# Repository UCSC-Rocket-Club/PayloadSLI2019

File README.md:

# Payload SLI 2019

## Summary
This is the code for deployment of the Payload for NASA's 2019 SLI Payload challenge. During flight, at approximately 400 feet, we will remotely trigger separation of the payload section via radio; and later trigger release of the drone. 

We are using the [Adafruit Feather LoRa 32u4 (RFM9x) with the RadioHead (RFM9x) library](https://learn.adafruit.com/adafruit-feather-32u4-radio-with-lora-radio-module/using-the-rfm-9x-radio). 

We are using the [Adafruit Micro-SD Breakout Board](https://cdn-learn.adafruit.com/downloads/pdf/adafruit-micro-sd-breakout-board-card-tutorial.pdf).

## Instructions to run
* Open the code in the Arduino IDE
* Follow [these steps](https://learn.adafruit.com/adafruit-feather-32u4-radio-with-lora-radio-module/setup) for installing the drivers for the Feather
* In `Arduino > Preferences`, under "Show verbose mode during" check both compilation and upload (this solves some issues with the board)
* Install the [RadioHead library](https://learn.adafruit.com/adafruit-feather-32u4-radio-with-lora-radio-module/using-the-rfm-9x-radio) (Note: Find the folder to put this in by going to Arduino -> Preferences -> Sketchbook location. Open this folder and there should be a folder called libraries in there. Put the unzipped library inside there.)

## Rules for this repo and all Payload code
* DO NOT SEND CODE OVER SLACK/IMESSAGE/FB
* Use branches and PRs -- this way we can do code reviews and learn git the proper way
* Write clean code
* Heavily comment your code, so that it's easier for people who aren't familiar with C/C++/coding in general to understand it
* Make flowcharts [with proper conventions](https://en.wikibooks.org/wiki/Programming_Fundamentals/Flowcharts) for the code you write so we can A) help visualize it and B) put in documents
* Record known issues in known issues
* The curly bracket must be on the same line as the function declaration

```
void myFunction() {
// Good
} 

void myShittyFunction() 
{
// Bad
}
```

## Troubleshooting 
### If the board is not recognized, follow these steps:
In Mac this state looks like nothing showing up under ports, on the PC it gives an error like "device not recognized". Check out the [Feather troubleshooting guide](https://learn.adafruit.com/adafruit-feather-32u4-radio-with-lora-radio-module/faq) for more info. 

1. First, double check that you have verbose mode enabled (see Instructions to run). 
2. Double check that your USB cable is not charge-only
3. Upload Blink (File -> Examples -> 0.1 Basics -> Blink), and hit the reset button shortly after clicking upload. The builtin LED should begin pulsing. 
3. If this doesn't work, follow the following steps to re-burn the bootloader:

### How to re-burn the bootloader:
The bootloader may need to be burned if you flash code that causes a program halt. This will result in the "board not recognized" issue. 

1. Obtain the bootloader ([Pololu USB AVR Programmer v2.1](https://www.pololu.com/docs/0J67/3)), a micro-USB cable, and a computer with Arduino IDE installed
2. Using a breadboard, connect the following: 

| Bootloader | Feather |
|------------|---------|
| GND        | GND     |
| MOSI       | MO      |
| VCC        | 3v      |
| RST        | RST     |
| SCK        | SCK     |
| MISO       | MI      |

3. Plug in the USB cable to the bootloader (NOT the feather) and your computer
4. Under ports, there should be two USB devices showing up. Select the first one (I'm not sure it matters, but this is what has always worked for me)
4. In the Arduino IDE, under `Tools > Programmer`, select "Atmel STK500 development board"
5. Click "Burn bootloader"

The board should now be recognized by your computer and able to flash. You can verify this by uploading Blink (`File -> Examples -> 0.1 Basics -> Blink`)

Be sure to not flash your bad code again so you don't have to repeat this!

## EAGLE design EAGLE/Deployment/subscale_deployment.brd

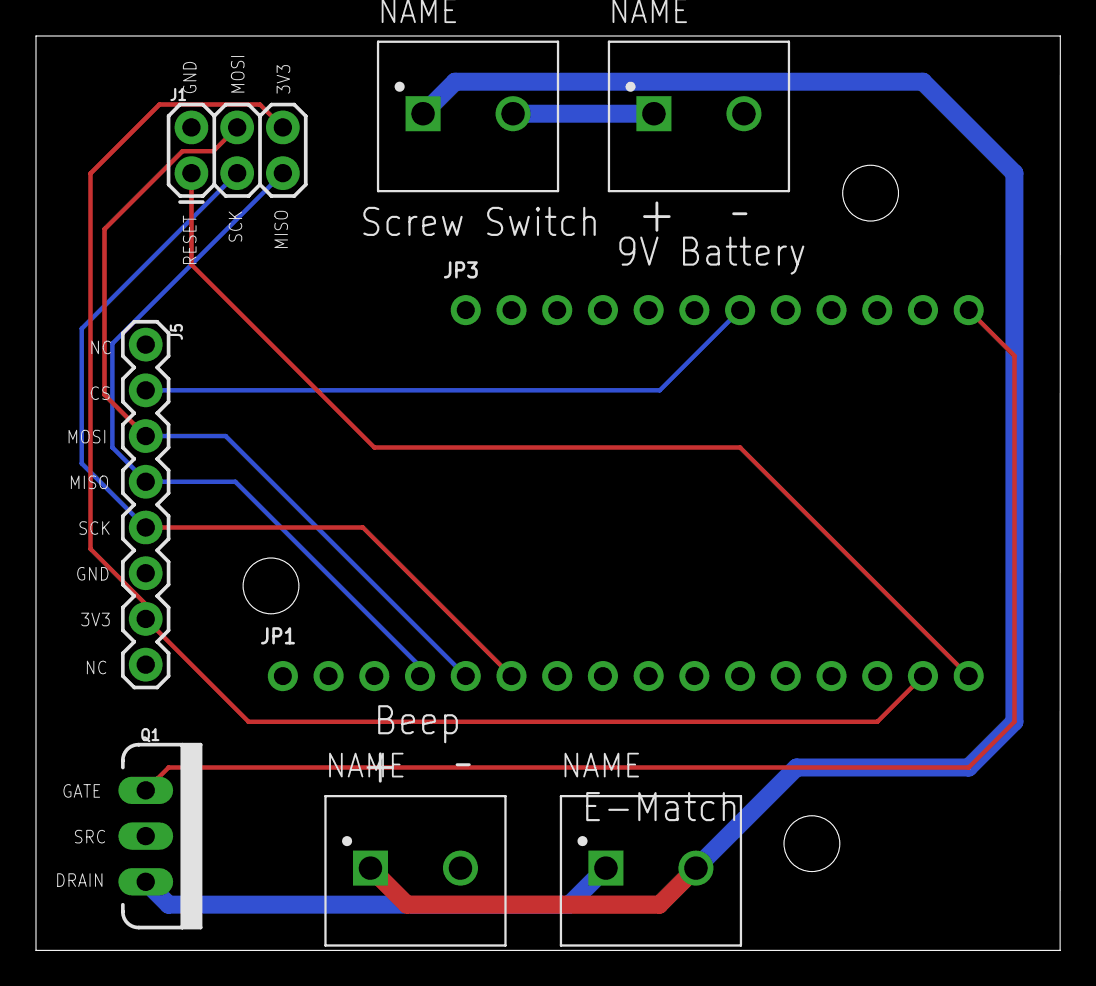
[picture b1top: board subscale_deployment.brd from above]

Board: 2 copper layers, 56.9 x 50.8 mm, 9 parts (0 on the bottom side), 11 nets.

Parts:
9V_BATT: 9V battery; PHOENIX_1935161
BUZZER: PHOENIX_1935161
E-MATCH: PHOENIX_1935161
J1: FEMALE 2x3; 2X3
J5: 1X08
JP1: 1X16_ROUND
JP3: 1X12_ROUND
Q1: 100V 14A; TO220V
SCREW_SWITCH: PHOENIX_1935161

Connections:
2: JP3.12, Q1.1
9V: BUZZER.1, E-MATCH.2, SCREW_SWITCH.1
10: J5.2, JP3.7
+3V3: J1.6, J5.7, JP1.15
BATT+: 9V_BATT.1, SCREW_SWITCH.2
GND: 9V_BATT.2, BUZZER.2, J1.2, J5.6, JP1.13, Q1.2
MISO: J1.5, J5.4, JP1.4
MOSI: J1.4, J5.3, JP1.5
unnamed: E-MATCH.1, Q1.3
RST: J1.1, JP1.16
SCK: J1.3, J5.5, JP1.6

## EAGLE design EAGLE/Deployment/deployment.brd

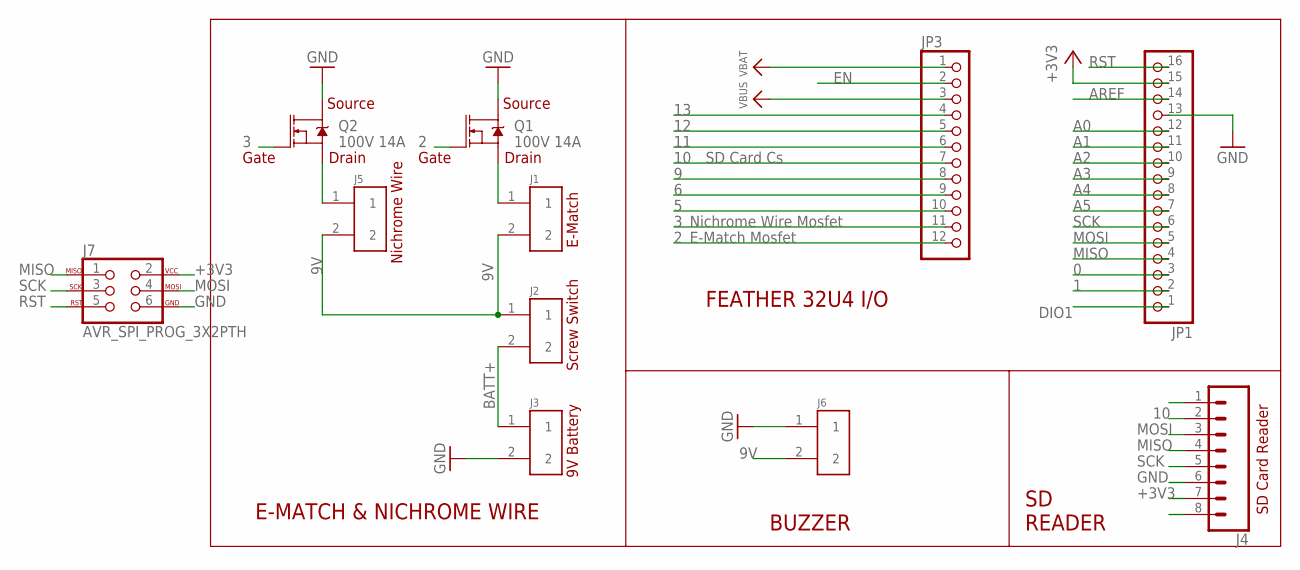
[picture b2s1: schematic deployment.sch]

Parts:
J1, J2, J3, J5, J6: 1935161; PHOENIX_1935161
J4: CONN_08"; 1X08
J7: AVR_SPI_PROG_3X2PTH; 2X3
JP1: HEADER-1X16ROUND; 1X16_ROUND
JP3: HEADER-1X12; 1X12_ROUND
Q1, Q2: 100V 14A; TO220V

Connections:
0: JP1.3
1: JP1.2
2: JP3.12, Q1.1 (G)
3: JP3.11, Q2.1 (G)
5: JP3.10
6: JP3.9
9: JP3.8
9V: J1.2, J2.1, J5.2, J6.2
10: J4.1, J4.2, JP3.7
11: JP3.6
12: JP3.5
13: JP3.4
+3V3: J4.7, J7.2, JP1.15
A0: JP1.12
A1: JP1.11
A2: JP1.10
A3: JP1.9
A4: JP1.8
A5: JP1.7
AREF: JP1.14
BATT+: J2.2, J3.1
DIO1: JP1.1
EN: JP3.2
GND: J3.2, J4.6, J6.1, J7.6, JP1.13, Q1.2 (D), Q2.2 (D)
MISO: J4.4, J7.1, JP1.4
MOSI: J4.3, J7.4, JP1.5
unnamed: J1.1, Q1.3 (S)
unnamed: J5.1, Q2.3 (S)
RST: J7.5, JP1.16
SCK: J4.5, J7.3, JP1.6
VBAT: JP3.1
VBUS: JP3.3

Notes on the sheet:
Gate
Source
Drain
E-Match
Screw Switch
SD Card Reader
E-MATCH & NICHROME WIRE
FEATHER 32U4 I/O
SD READER
BUZZER
9V Battery
E-Match Mosfet
SD Card Cs
Nichrome Wire
Nichrome Wire Mosfet

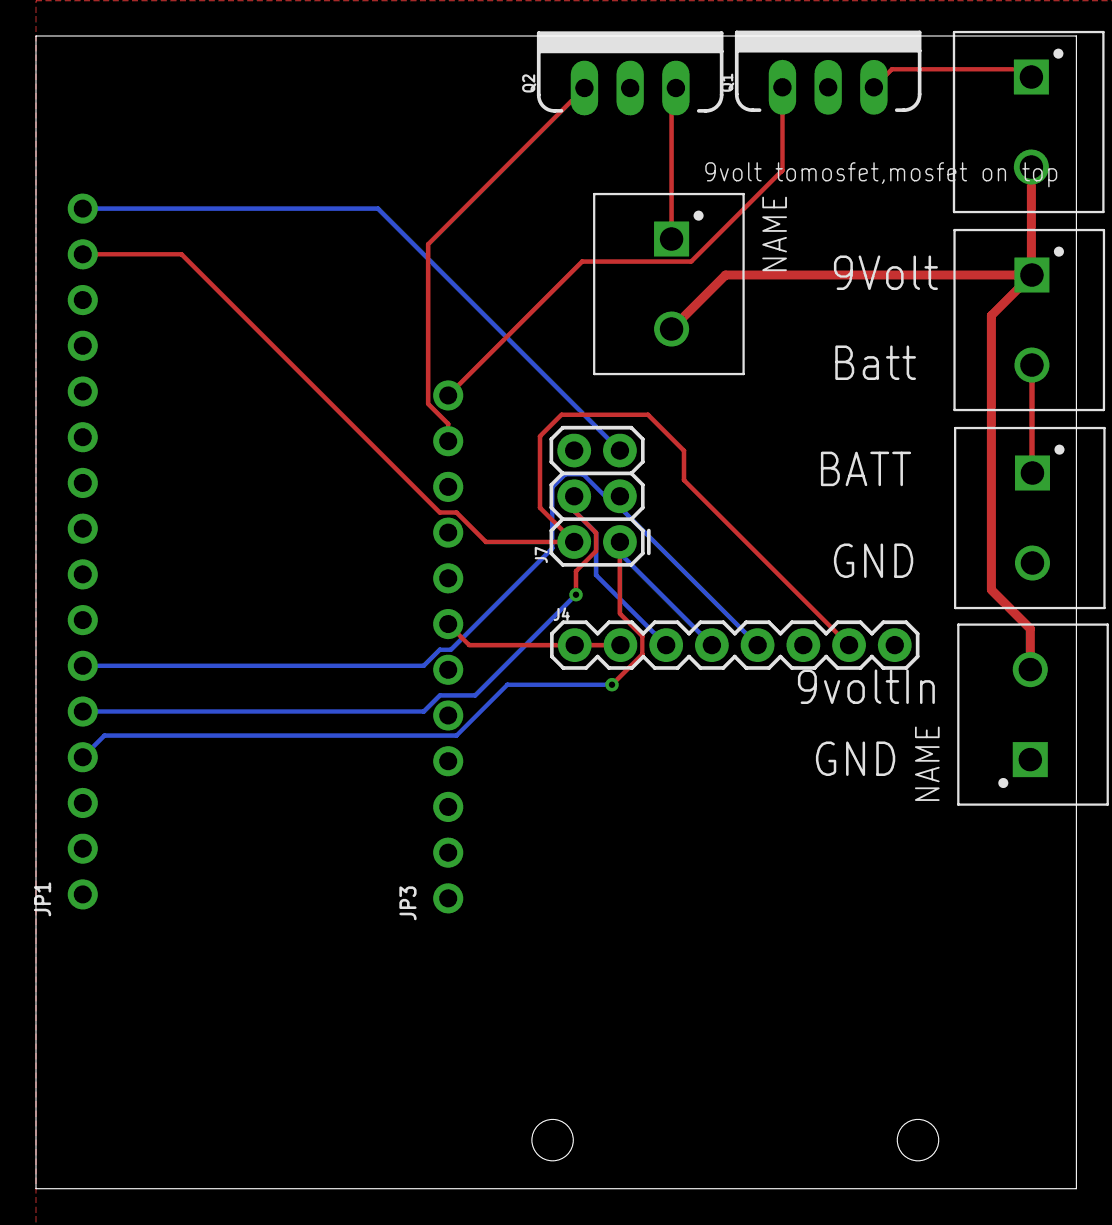
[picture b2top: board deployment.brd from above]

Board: 2 copper layers, 57.8 x 64.0 mm, 11 parts (0 on the bottom side), 13 nets.

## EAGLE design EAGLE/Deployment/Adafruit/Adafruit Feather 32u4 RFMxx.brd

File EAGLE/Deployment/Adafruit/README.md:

## Adafruit Feather 32u4 RFM LoRa Radios PCB

<br/>
Click below to purchase one from the Adafruit shop

PCB files for the Adafruit Feather 32u4 RFM69 and LoRa Radio. Format is EagleCAD schematic and board layout

For more details, check out the product pages at
* RFM69HCW Packet Radio - 868 or 915 MHz https://www.adafruit.com/product/3076
* RFM69HCW Packet Radio - 433MHz https://www.adafruit.com/product/3077
* RFM95 LoRa Radio- 868 or 915 MHz https://www.adafruit.com/product/3078
* RFM96 LoRa Radio - 433MHz https://www.adafruit.com/product/3079

### Description

We call these RadioFruits, our take on an microcontroller packet radio transceiver with built in USB and battery charging. Its an Adafruit Feather 32u4 with a radio module cooked in! Great for making wireless networks that can go further than 2.4GHz 802.15.4 and similar, are more flexible than Bluetooth LE and without the high power requirements of WiFi.

Feather is the new development board from Adafruit, and like its namesake it is thin, light, and lets you fly! We designed Feather to be a new standard for portable microcontroller cores.

### License

Adafruit invests time and resources providing this open source design, please support Adafruit and open-source hardware by purchasing products from [Adafruit](https://www.adafruit.com)!

Designed by Limor Fried/Ladyada for Adafruit Industries.

Creative Commons Attribution/Share-Alike, all text above must be included in any redistribution. See license.txt for additional details.

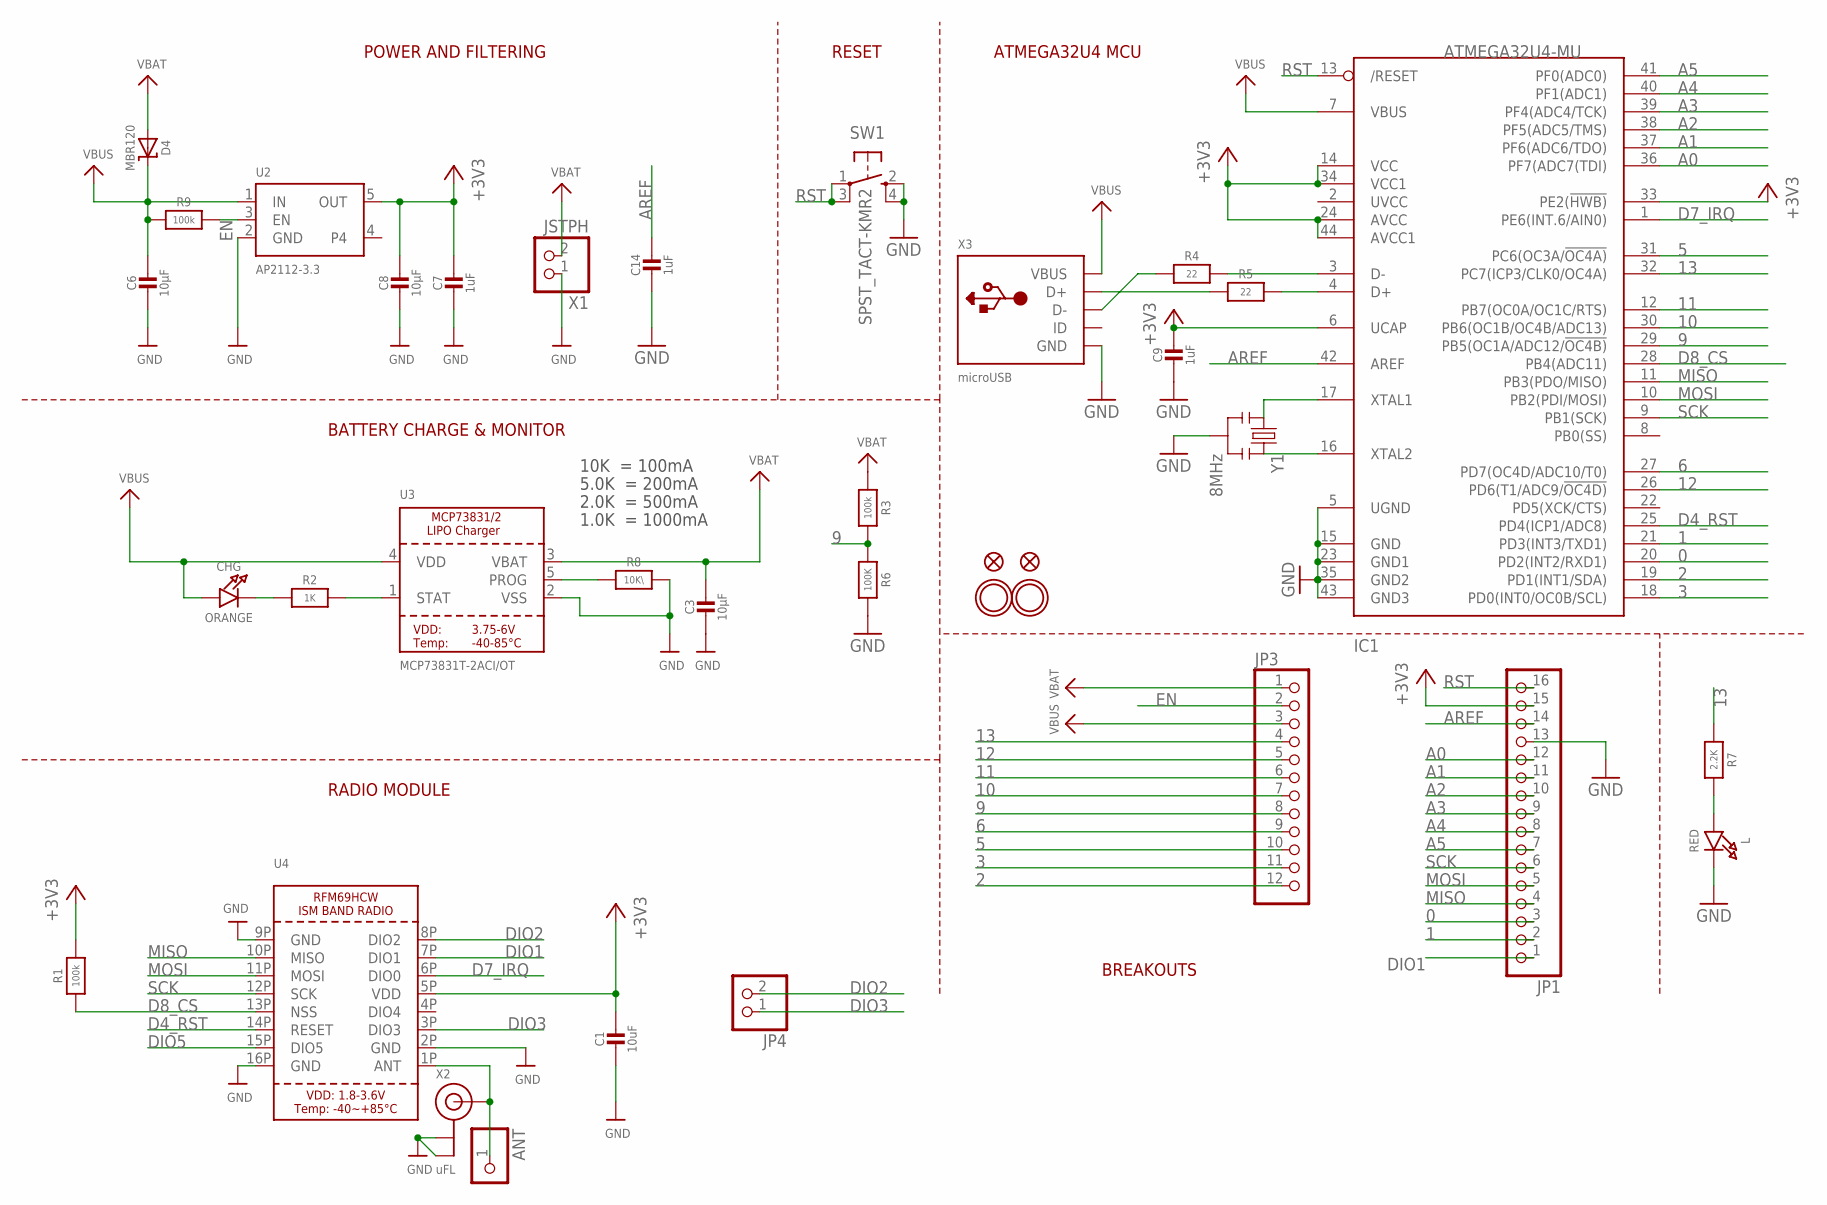
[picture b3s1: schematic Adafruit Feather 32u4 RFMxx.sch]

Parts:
ANT: HEADER-1X1ROUND; 1X01_ROUND
C1: 10uF; 0805-NO
C3, C6, C8: 10µF; 0805-NO
C7, C14: 1uF; 0603-NO
C9: 1uF; _0603MP
CHG: ORANGE; CHIPLED_0805_NOOUTLINE
D4: MBR120; SOD-123
IC1: ATMEGA32U4-MU; TQFN44_7MM
JP1: HEADER-1X16ROUND; 1X16_ROUND
JP3: HEADER-1X12; 1X12_ROUND
JP4: HEADER-1X2ROUND; 1X02_ROUND
L: RED; CHIPLED_0805_NOOUTLINE
R1, R3, R9: 100k; 0603-NO
R2: 1K; 0603-NO
R4, R5: 22; 0603-NO
R6: 100K; 0603-NO
R7: 2.2K; 0603-NO
R8: 10K\; 0603-NO
SW1: SPST_TACT-KMR2; KMR2
U2: AP2112-3.3; SOT23-5
U3: MCP73831T-2ACI/OT; SOT23-5
U4: RFM69HCW_SMT; RFMHCW_SMT
U$31, U$32: MOUNTINGHOLE2.5; MOUNTINGHOLE_2.5_PLATED
U$34, U$35: FIDUCIAL""; FIDUCIAL_1MM
X1: JSTPH; JSTPH2
X2: uFL; U.FL
X3: microUSB; 4UCONN_20329_V2
Y1: 8MHz; RESONATOR-SMD

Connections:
0: IC1.20 (PD2(INT2/RXD1)), JP1.3
1: IC1.21 (PD3(INT3/TXD1)), JP1.2
2: IC1.19 (PD1(INT1/SDA)), JP3.12
3: IC1.18 (PD0(INT0/OC0B/SCL)), JP3.11
5: IC1.31 (PC6(OC3A/!OC4A)), JP3.10
6: IC1.27 (PD7(OC4D/ADC10/T0)), JP3.9
9: IC1.29 (PB5(OC1A/ADC12/!OC4B)), JP3.8, R3.2, R6.1
10: IC1.30 (PB6(OC1B/OC4B/ADC13)), JP3.7
11: IC1.12 (PB7(OC0A/OC1C/RTS)), JP3.6
12: IC1.26 (PD6(T1/ADC9/!OC4D)), JP3.5
13: IC1.32 (PC7(ICP3/CLK0/OC4A)), JP3.4, R7.1
+3V3: C1.1, C7.1, C8.1, C9.1, IC1.6 (UCAP), IC1.14 (VCC), IC1.24 (AVCC), IC1.33 (PE2(!HWB)), IC1.34 (VCC1), IC1.44 (AVCC1), JP1.15, R1.2, U2.5 (OUT), U4.5P (VDD)
A0: IC1.36 (PF7(ADC7(TDI)), JP1.12
A1: IC1.37 (PF6(ADC6/TDO)), JP1.11
A2: IC1.38 (PF5(ADC5/TMS)), JP1.10
A3: IC1.39 (PF4(ADC4/TCK)), JP1.9
A4: IC1.40 (PF1(ADC1)), JP1.8
A5: IC1.41 (PF0(ADC0)), JP1.7
ANT: ANT.1, U4.1P (ANT), X2.3 (SIGNAL)
AREF: C14.1, IC1.42 (AREF), JP1.14
D4_RST: IC1.25 (PD4(ICP1/ADC8)), U4.14P (RESET)
D7_IRQ: IC1.1 (PE6(INT.6/AIN0)), U4.6P (DIO0)
D8_CS: IC1.28 (PB4(ADC11)), R1.1, U4.13P (NSS)
D+: IC1.4 (D+), R5.2
D-: IC1.3 (D-), R4.2
DIO1: JP1.1, U4.7P (DIO1)
DIO2: JP4.2, U4.8P (DIO2)
DIO3: JP4.1, U4.3P (DIO3)
DIO5: U4.15P (DIO5)
EN: JP3.2, R9.2, U2.3 (EN)
GND: C1.2, C3.2, C6.2, C7.2, C8.2, C9.2, C14.2, IC1.5 (UGND), IC1.15 (GND), IC1.23 (GND1), IC1.35 (GND2), IC1.43 (GND3), JP1.13, L.C, R6.2, R8.2, SW1.2 (S), SW1.4 (S1), U2.2 (GND), U3.2 (VSS), U4.2P (GND), U4.9P (GND), U4.16P (GND), X1.1, X2.1 (GND), X2.2 (GND), X3.BASE@1 (GND), X3.BASE@2 (GND), X3.GND, X3.SPRT@1 (GND), X3.SPRT@2 (GND), X3.SPRT@3 (GND), X3.SPRT@4 (GND), Y1.2
MISO: IC1.11 (PB3(PDO/MISO)), JP1.4, U4.10P (MISO)
MOSI: IC1.10 (PB2(PDI/MOSI)), JP1.5, U4.11P (MOSI)
unnamed: CHG.C, R2.1
unnamed: L.A, R7.2
unnamed: R2.2, U3.1 (STAT)
unnamed: R8.1, U3.5 (PROG)
unnamed: IC1.16 (XTAL2), Y1.3
unnamed: IC1.17 (XTAL1), Y1.1
unnamed: R5.1, X3.D+
unnamed: R4.1, X3.D-
RST: IC1.13 (/RESET), JP1.16, SW1.1, SW1.3 (P1)
SCK: IC1.9 (PB1(SCK)), JP1.6, U4.12P (SCK)
VBAT: C3.1, D4.A, JP3.1, R3.1, U3.3 (VBAT), X1.2
VBUS: C6.1, CHG.A, D4.C, IC1.7 (VBUS), JP3.3, R9.1, U2.1 (IN), U3.4 (VDD), X3.VBUS

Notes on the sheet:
POWER AND FILTERING
RESET
ATMEGA32U4 MCU
10K = 100mA
5.0K = 200mA
2.0K = 500mA
1.0K = 1000mA
BATTERY CHARGE & MONITOR
BREAKOUTS
RADIO MODULE

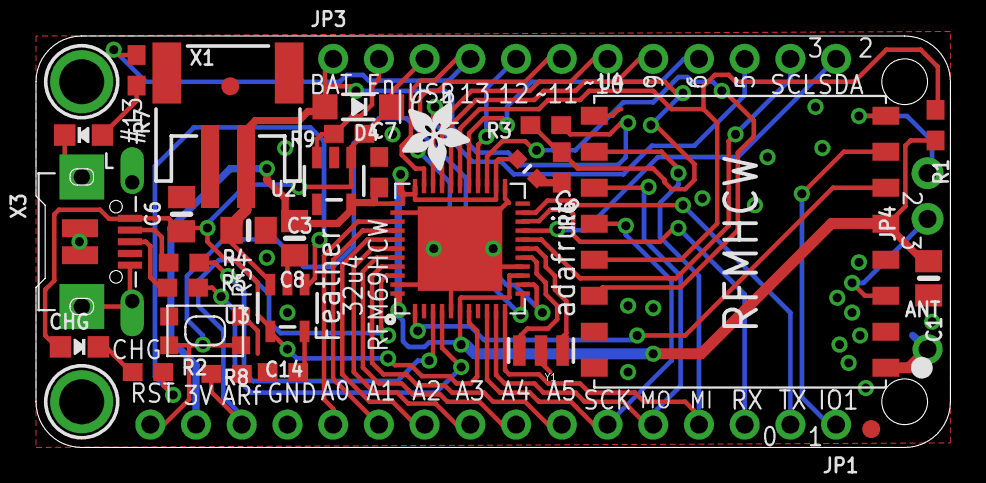
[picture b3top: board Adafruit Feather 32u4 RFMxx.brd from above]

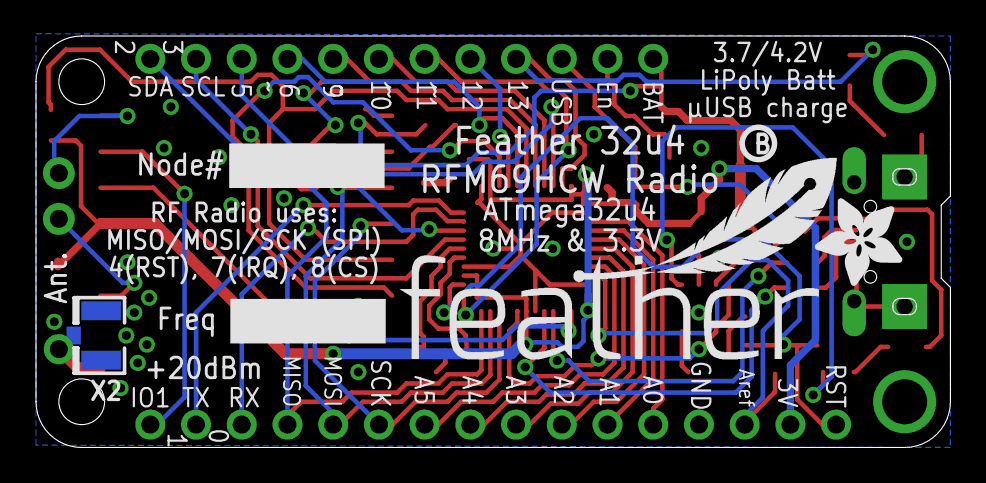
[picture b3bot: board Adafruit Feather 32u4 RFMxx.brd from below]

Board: 2 copper layers, 50.8 x 22.9 mm, 40 parts (4 on the bottom side), 44 nets.

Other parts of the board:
U$4: ADAFRUIT_5MM
U$5: FEATHERLOGO
U$6: PCBFEAT-REV-040
U$7: ADAFRUIT_3.5MM

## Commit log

2019-12-10 fixed sketch name
2019-12-10 actually added my files
2019-12-10 Set all Serial to optional grouping thing
2020-01-03 added transmitter code
2020-01-03 transmitter code added
2020-01-03 refactored
2020-01-03 refactored and made it print all pretty :)
2020-01-03 Created directory /EAGLE to store schematic and board files, added deployment.sch schematic of the deployment circuit
2020-01-03 Added nichrome wire circuit to deployment schematic
2020-01-03 Fixed wiring of nichrome wire circit in the depolyment schematic
2020-01-03 Fixed issue with buzzer wiring
2020-01-03 Commented out all serial code for the reciever
2020-01-04 it works
2020-01-04 Added subscale deployment schematic
2020-01-05 updated readme to include bootloader burning
2020-01-05 upadated readme
2020-01-06 Fixed bootloader terminology in README
2020-01-06 starts deployment for full scale board
2020-01-06 starts full scale deployment circuitboard, neeeds design review and imu
2020-01-06 fixes trace width on full scale deployment board
2020-01-06 Completed layout and routing of subscale deployment PCB
2020-01-06 uncorrupted hopefully
2020-01-15 Fixed formatting
2020-01-15 Fixed merge conflict with bootloader vs ISP Flasher
2020-01-16 SD card reader
2020-01-16 Added link to SD card reader documentation.
2020-01-17 Added a logging function to the receiver's program. Log function does not currently function properly. I suspect it may be an issue with wiring to mosi or the pins are being turned on and off at the 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
2020-01-23 Changed SD pin
2020-01-24 I'm making this code hurt me less
2020-01-24 Implemented SD card writes and chip select, need to fix loop()
2020-01-24 Finished reorganization of receiver code
2020-01-24 Added chip select deactivation at the end of radio setup and SD setup
2020-01-24 I think I broke it
2020-01-24 Bad?
2020-01-24 Comments are good
2020-01-24 Rewrote sdTest() so that it's useful
2020-01-24 Added some more serial prints to sdTest()
2020-01-24 mmmmmmmmmmmmmmmmmm
2020-01-24 Removed one of the existance tests
2020-01-24 It almost works
2020-01-31 New recevier code in receiver with sd folder
2020-02-01 changed led blink, pin
2020-02-01 Removed SD functionality I think

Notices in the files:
parts and their libraries:
microbuilder: This work is placed in the public domain, and may be freely used for commercial and non-commercial work with the following conditions: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
SparkFun: Licensing: CC v3.0 Share-Alike You are welcome to use this library for commercial purposes.
